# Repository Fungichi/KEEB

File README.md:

# Fatman 1.0

My DIY mechanical keyboard (sandwich mount). It has ***28 keys*** of which 4 are 3u keys. This keyboard is especially designed to play games that were meant to be played on a ***controller**: each key replaces a part of the controller. It is ideal for rhytm games, Tetris, Mortal Kombat and many other retro games.

# Why
My goal was to get a first feeling with hardware/pcb's. I think this is the perfect project to start with pcb's because the electronics part was pretty simple. That aside I do regret spending so much time on the case, as I think this is rather boring.

# The result
The keyboard will be shown down below when I get the parts.
What I learned:
- What makes up a keyboard
- How a switch matrix is constructed
- Making schematics in KiCad 10.0
- Designing the pcb in KiCad 10.0
- Designing an object in Onshape

## Schematic

## Pcb

## Case

You can see my learning process in the [Devlogs](devlogs/README.md)

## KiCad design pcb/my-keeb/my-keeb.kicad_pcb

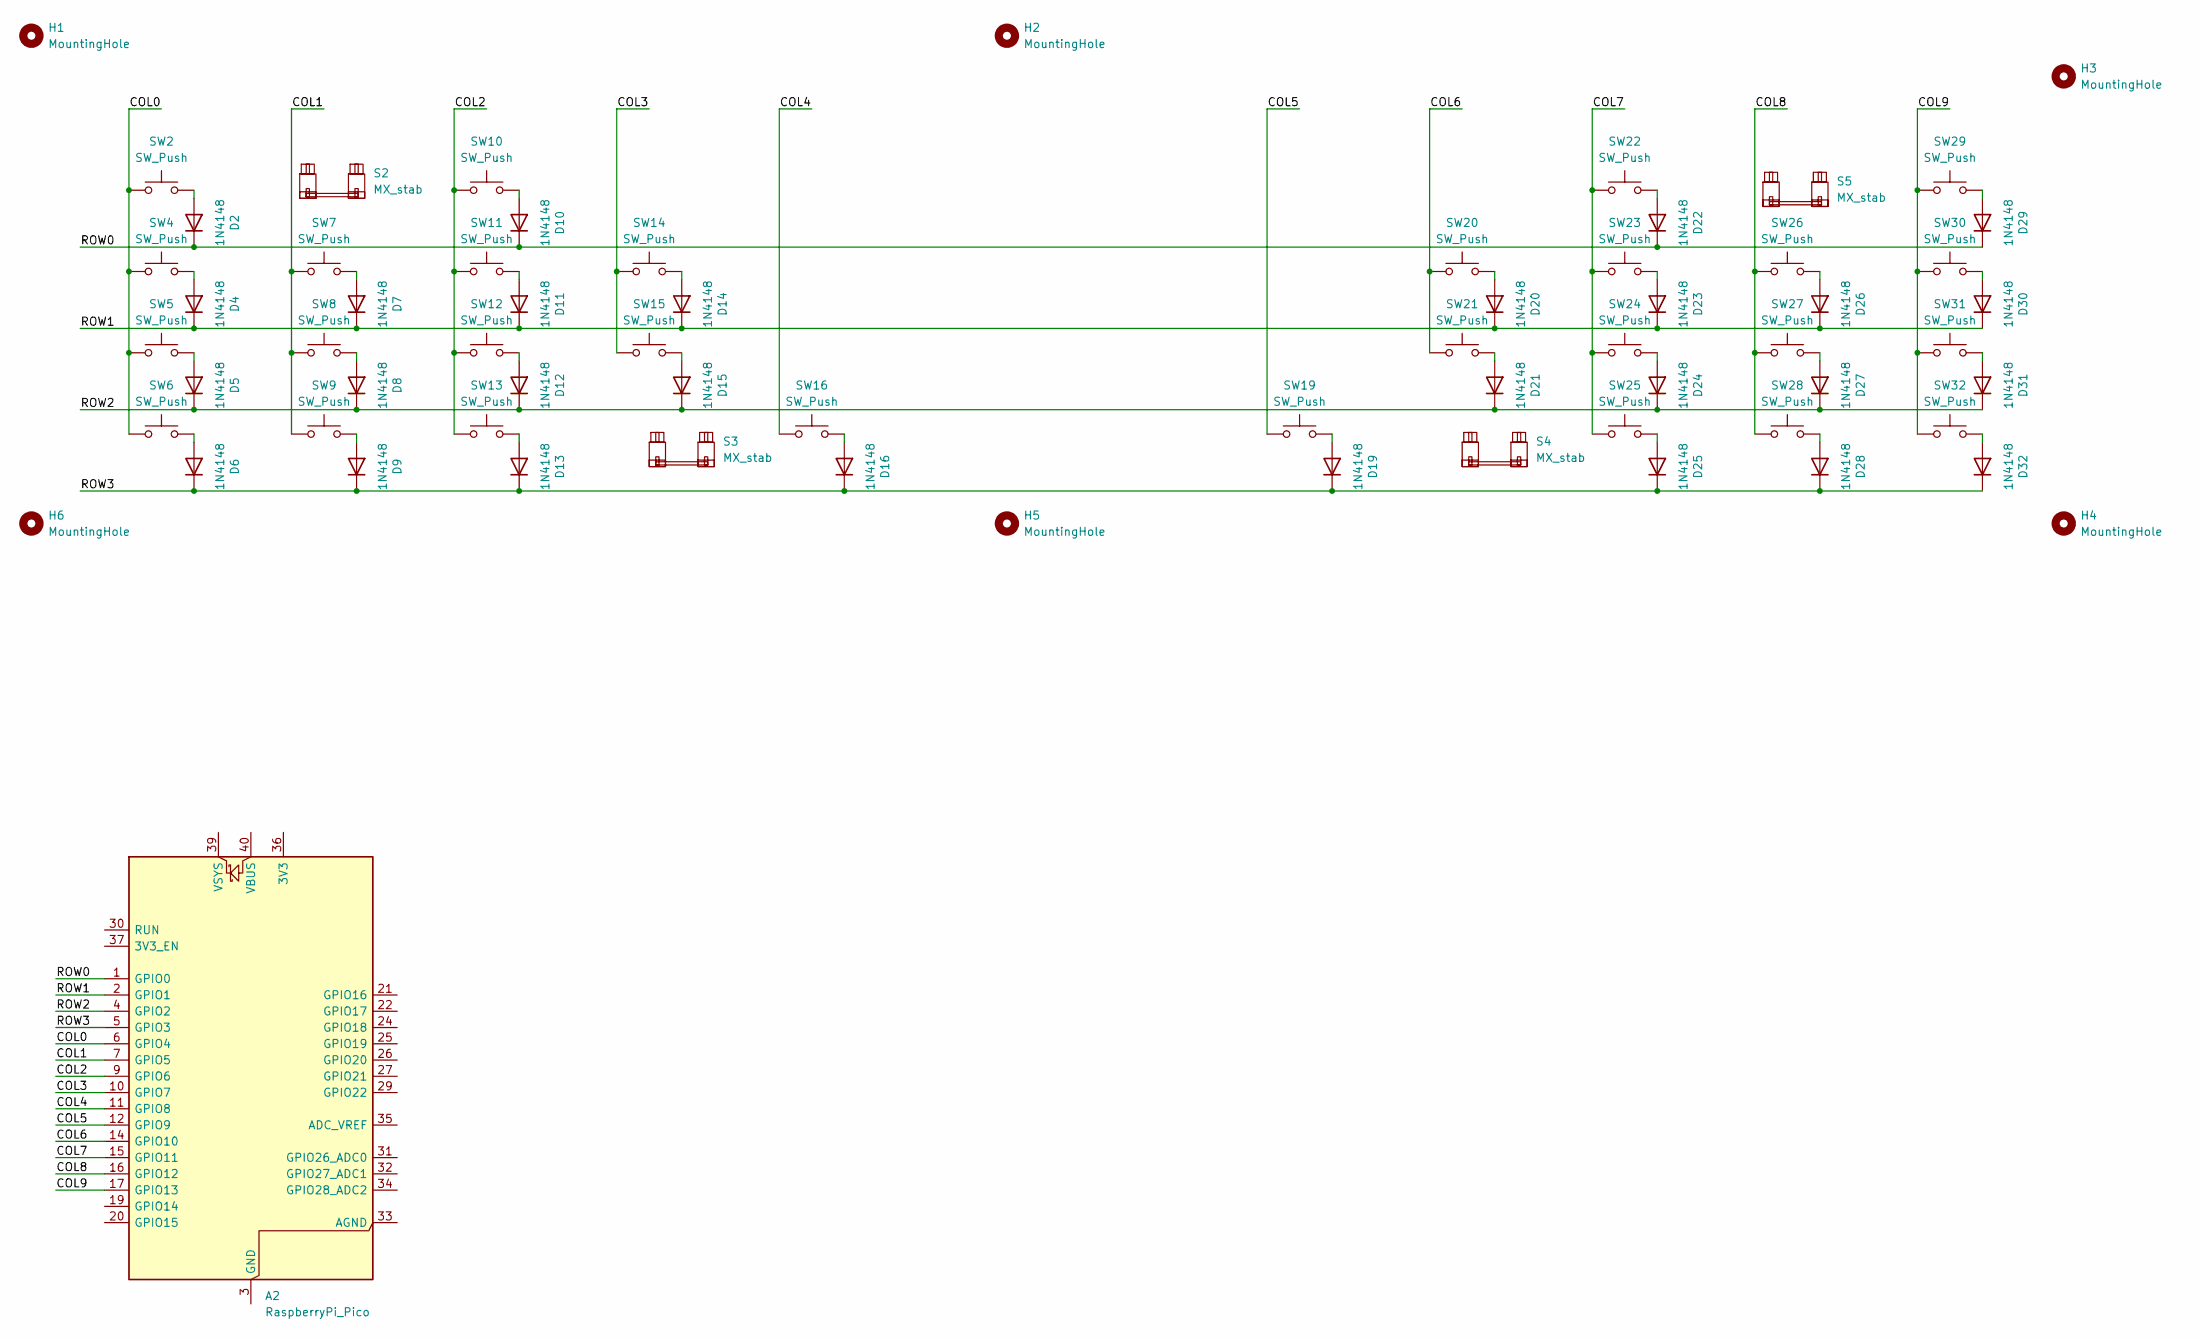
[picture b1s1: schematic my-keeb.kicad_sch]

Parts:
A2: RaspberryPi_Pico; RaspberryPi_Pico_Common_THT
D2, D4, D5, D6, D7, D8, D9, D10, D11, D12, D13, D14, D15, D16, D19, D20, D21, D22, D23, D24, D25, D26, D27, D28, D29, D30, D31, D32: 1N4148; D_DO-35_SOD27_P7.62mm_Horizontal
H1, H2, H3, H4, H5, H6: MountingHole
S2, S3, S4, S5: MX_stab; STAB_MX_3u
SW2, SW4, SW5, SW6, SW7, SW8, SW9, SW10, SW11, SW12, SW13, SW14, SW15, SW16, SW19, SW20, SW21, SW22, SW23, SW24, SW25, SW26, SW27, SW28, SW29, SW30, SW31, SW32: SW_Push; SW_MX_1u

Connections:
/<NO NET>: A2.10 (GPIO7), SW14.1, SW15.1
/COL0: A2.6 (GPIO4), SW2.1, SW4.1, SW5.1, SW6.1
/COL1: A2.7 (GPIO5), SW7.1, SW8.1, SW9.1
/COL2: A2.9 (GPIO6), SW10.1, SW11.1, SW12.1, SW13.1
/COL4: A2.11 (GPIO8), SW16.1
/COL5: A2.12 (GPIO9), SW19.1
/COL6: A2.14 (GPIO10), SW20.1, SW21.1
/COL7: A2.15 (GPIO11), SW22.1, SW23.1, SW24.1, SW25.1
/COL8: A2.16 (GPIO12), SW26.1, SW27.1, SW28.1
/COL9: A2.17 (GPIO13), SW29.1, SW30.1, SW31.1, SW32.1
/ROW0: A2.1 (GPIO0), D2.1 (K), D10.1 (K), D22.1 (K), D29.1 (K)
/ROW1: A2.2 (GPIO1), D4.1 (K), D7.1 (K), D11.1 (K), D14.1 (K), D20.1 (K), D23.1 (K), D26.1 (K), D30.1 (K)
/ROW2: A2.4 (GPIO2), D5.1 (K), D8.1 (K), D12.1 (K), D15.1 (K), D21.1 (K), D24.1 (K), D27.1 (K), D31.1 (K)
/ROW3: A2.5 (GPIO3), D6.1 (K), D9.1 (K), D13.1 (K), D16.1 (K), D19.1 (K), D25.1 (K), D28.1 (K), D32.1 (K)
unnamed: A2.3 (GND), A2.8 (GND), A2.13 (GND), A2.18 (GND), A2.23 (GND), A2.28 (GND), A2.38 (GND)
unnamed: D2.2 (A), SW2.2
unnamed: D4.2 (A), SW4.2
unnamed: D5.2 (A), SW5.2
unnamed: D6.2 (A), SW6.2
unnamed: D7.2 (A), SW7.2
unnamed: D8.2 (A), SW8.2
unnamed: D9.2 (A), SW9.2
unnamed: D10.2 (A), SW10.2
unnamed: D11.2 (A), SW11.2
unnamed: D12.2 (A), SW12.2
unnamed: D13.2 (A), SW13.2
unnamed: D14.2 (A), SW14.2
unnamed: D15.2 (A), SW15.2
unnamed: D16.2 (A), SW16.2
unnamed: D19.2 (A), SW19.2
unnamed: D20.2 (A), SW20.2
unnamed: D21.2 (A), SW21.2
unnamed: D22.2 (A), SW22.2
unnamed: D23.2 (A), SW23.2
unnamed: D24.2 (A), SW24.2
unnamed: D25.2 (A), SW25.2
unnamed: D26.2 (A), SW26.2
unnamed: D27.2 (A), SW27.2
unnamed: D28.2 (A), SW28.2
unnamed: D29.2 (A), SW29.2
unnamed: D30.2 (A), SW30.2
unnamed: D31.2 (A), SW31.2
unnamed: D32.2 (A), SW32.2

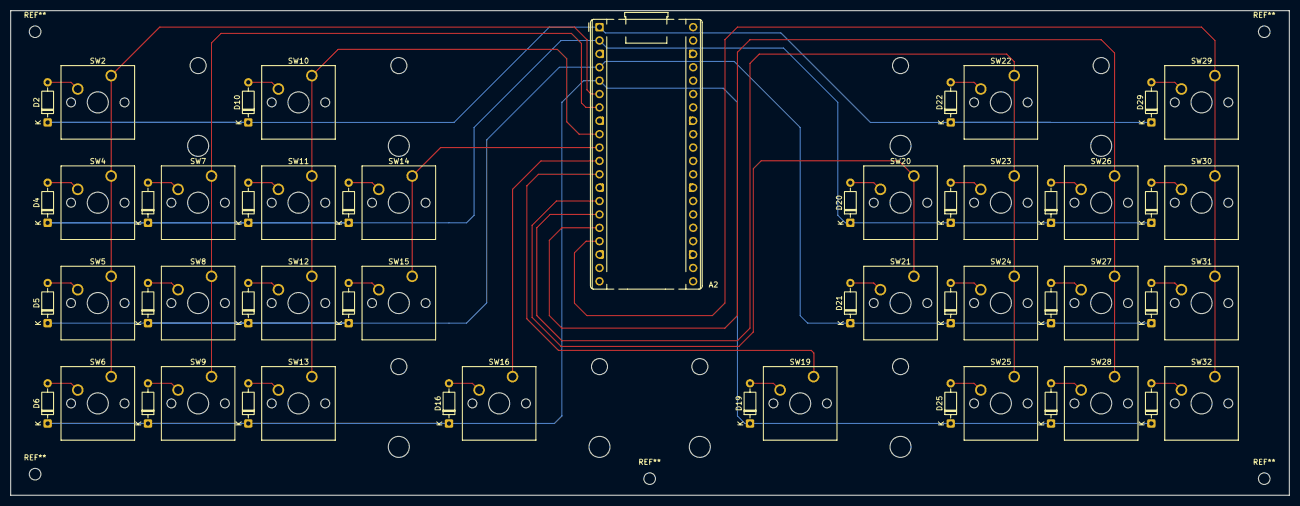
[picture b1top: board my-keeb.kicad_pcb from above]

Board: 2 copper layers, 242.8 x 92.0 mm, 61 parts (0 on the bottom side), 43 nets.
